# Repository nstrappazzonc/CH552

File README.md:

# Microcontroller CH552G by a hobbyist

This is a fascinating, enhanced, and well-equipped 8-bit microcontroller, available at an incredibly low cost (around $1), designed and manufactured in China by [Jiangsu Heng Qin Ltd. (WCH)](http://www.wch-ic.com). For now, we will focus on the [CH552G](https://www.wch-ic.com/products/CH552.html), which is based on the E8051 architecture. One of the most appealing features of this MCU is its USB port and a 24MHz internal oscillator, among other functionalities. Programming it requires a strong foundation in [MCS-51/80C51](https://en.wikipedia.org/wiki/MCS-51). The manufacturer provides a [package with a wide variety of source codes](https://www.wch.cn/downloads/CH552EVT_ZIP.html). There are different package options and versions of the MCU, such as the CH551, CH552, CH554, and CH559. The USB port, with its multiple functions, allows for easy program uploads, posing no risk as it is a native feature. In my personal opinion, this microcontroller is ideal for hobbyists working on simple projects or for those with a curious mindset.

A major difference of this microcontroller compared to other microcontrollers is that it does not require an additional device for programming; the USB port is sufficient. I believe that using a push button to access the bootloader for programming adds an extra level of security.

You can purchase the MCUs from the official store on [AliExpress](https://wchofficialstore.es.aliexpress.com/store/1100367542) or at [LCSC](https://www.lcsc.com).

For example, an MCU from the AT89LP51 family offers fewer features and costs three times more compared to the CH55X family. Of course, the support community for Microchip is much larger and more established compared to WCH’s, which is just starting to grow. However, the key is having good official documentation and a solid architecture. With patience and perseverance, great things can be achieved.

## Specifications

Here are the most relevant specifications of the MCU. For more details, refer to the [official documentation](https://www.wch-ic.com/products/CH552.html).

- Operates between 5V and 3.3V.
- Includes 16KB Code Flash, 1KB XRAM, 256B iRAM, and 128B DataFlash.
- Supports USB 2.0, UART, SPI, and ISP communication protocols.
- Features 3 timers, 2 signal capture units, 2 PWM, and 4 ADC.
- Equipped with a BootLoader.
- Includes a 24MHz internal clock.
- Comes with a unique numeric identifier.
- Available packages: TSSOP-20, SOP-16, MSOP-10.

The pinout we are showing is basic, just to give you an idea. There are more functionalities available on the ports. Please refer to the [datasheet](https://github.com/nstrappazzonc/CH552/blob/main/doc/CH552.pdf?raw=true) for more detailed information.

> [!IMPORTANT]
> 1. The internal 24MHz clock is not precise but in the most cases is good, you can adjust it by software using a logic analyze, otherwise you will have to use an external one.
> 2. It’s worth noting that there is a limitation with the ROM or Code Flash, as it uses an iFlash™ process, which can be programmed approximately 10,000 times before the Flash memory may begin to degrade or fail. However, this value can vary > slightly depending on factors such as operating temperature and proper handling of write cycles. In any case, it is enough.

## Minimum Schematic

Use the following components to build the minimum circuit:

- One CH552G microcontroller.
- Two 100nF capacitors.
- Two 10K resistors.
- Two 1K resistors.
- Two push buttons: one for boot and one for reset.

On the breadboard, it should look like this:

## Source Code

This repository contains a collection of example source codes written in C to get started. All the listed examples have been thoroughly tested to ensure they function correctly.

- [adc](https://github.com/nstrappazzonc/CH552/tree/main/src/adc) Captures voltage variations through an input port.
- [blink](https://github.com/nstrappazzonc/CH552/tree/main/src/blink) Uses an output port to turn an LED on and off.
- [bootloader](https://github.com/nstrappazzonc/CH552/tree/main/src/bootloader) Forces the MCU to enter bootloader mode by default.
- [button & led rgb](https://github.com/nstrappazzonc/CH552/tree/main/src/button_led_rgb) Interacts with a button and an RGB LED to change its color.
- [button](https://github.com/nstrappazzonc/CH552/tree/main/src/button) Uses one input port for a button and another output port for the LED.
- [cdc](https://github.com/nstrappazzonc/CH552/tree/main/src/cdc) Sends and receives messages via the UART protocol.
- [data flash](https://github.com/nstrappazzonc/CH552/tree/main/src/data_flash) Saves the last state in persistent memory.
- [DHT11](https://github.com/nstrappazzonc/CH552/tree/main/src/dht11) Read DHT11 sensor and print to OLED module.
- [fade](https://github.com/nstrappazzonc/CH552/tree/main/src/fade) Uses PWM to fade a LED on and off.
- [oled module](https://github.com/nstrappazzonc/CH552/tree/main/src/ssd1306) Simple usage of an OLED module with I2C.
- [USB/cdc](https://github.com/nstrappazzonc/CH552/tree/main/src/usb/cdc/tx) Sends messages via the USB port.

## Documentation

This is basic documentation to help you compile and upload firmware to the MCU, including the datasheet, relevant links, and much more.

- [SDCC (Small Devices C Compiler)](https://github.com/nstrappazzonc/CH552/blob/main/doc/sdcc.md) Explains how to install and use the compiler.
- [Bootloader](https://github.com/nstrappazzonc/CH552/blob/main/doc/flash.md) The MCU has a bootloader, and you need to know how to enter it to upload the firmware.
- [Datasheet](https://github.com/nstrappazzonc/CH552/blob/main/doc/CH552.pdf) Technical documentation from the manufacturer.

## Related Projects

- [CH334 - HUB USB 2.0](https://github.com/nstrappazzonc/CH334)
- [CH340 - USB 2.0 to Serial](https://github.com/nstrappazzonc/CH340)
- [CH9141 - Bluetooth Serial Transparent](https://github.com/nstrappazzonc/CH9141)

## Third-Party Projects

- [Adafruit CH552 QT Py](https://learn.adafruit.com/adafruit-ch552-qt-py/overview)
- [English Docs for CH559 Microcontroller](https://kprasadvnsi.github.io/CH559_Doc_English)
- [Small Devices Arduino for ch55x devices](https://github.com/DeqingSun/ch55xduino)

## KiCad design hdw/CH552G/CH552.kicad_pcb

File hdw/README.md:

# Hardware

En este directorio hay una serie de proyectos hechos con [KiCad](https://www.kicad.org) relacionados al CH552G.

Las placas se pueden mandar a construir en [JLCPCB](https://jlcpcb.com).

- [Minimal](https://github.com/nstrappazzonc/CH552/tree/main/hdw/minimal) Esquema mínimo del circuito para el CH552G.

- [Breakout SOIC16](https://github.com/nstrappazzonc/CH552/tree/main/hdw/SOIC16) Una simple PCB para poder soldar el CH552G y poder trabajar en el protoboard.

- [Breakout USB-C 2.0](https://github.com/nstrappazzonc/CH552/tree/main/hdw/USBC2) Una simple PCB para poder soldar el conector USB-C 2.0 y poder trabajar en el protoboard teniendo un excelente soporte que lo fija bien.

- [Breakout CH552G](https://github.com/nstrappazzonc/CH552/tree/main/hdw/CH552G) Una PCB con el circuito del CH552G.

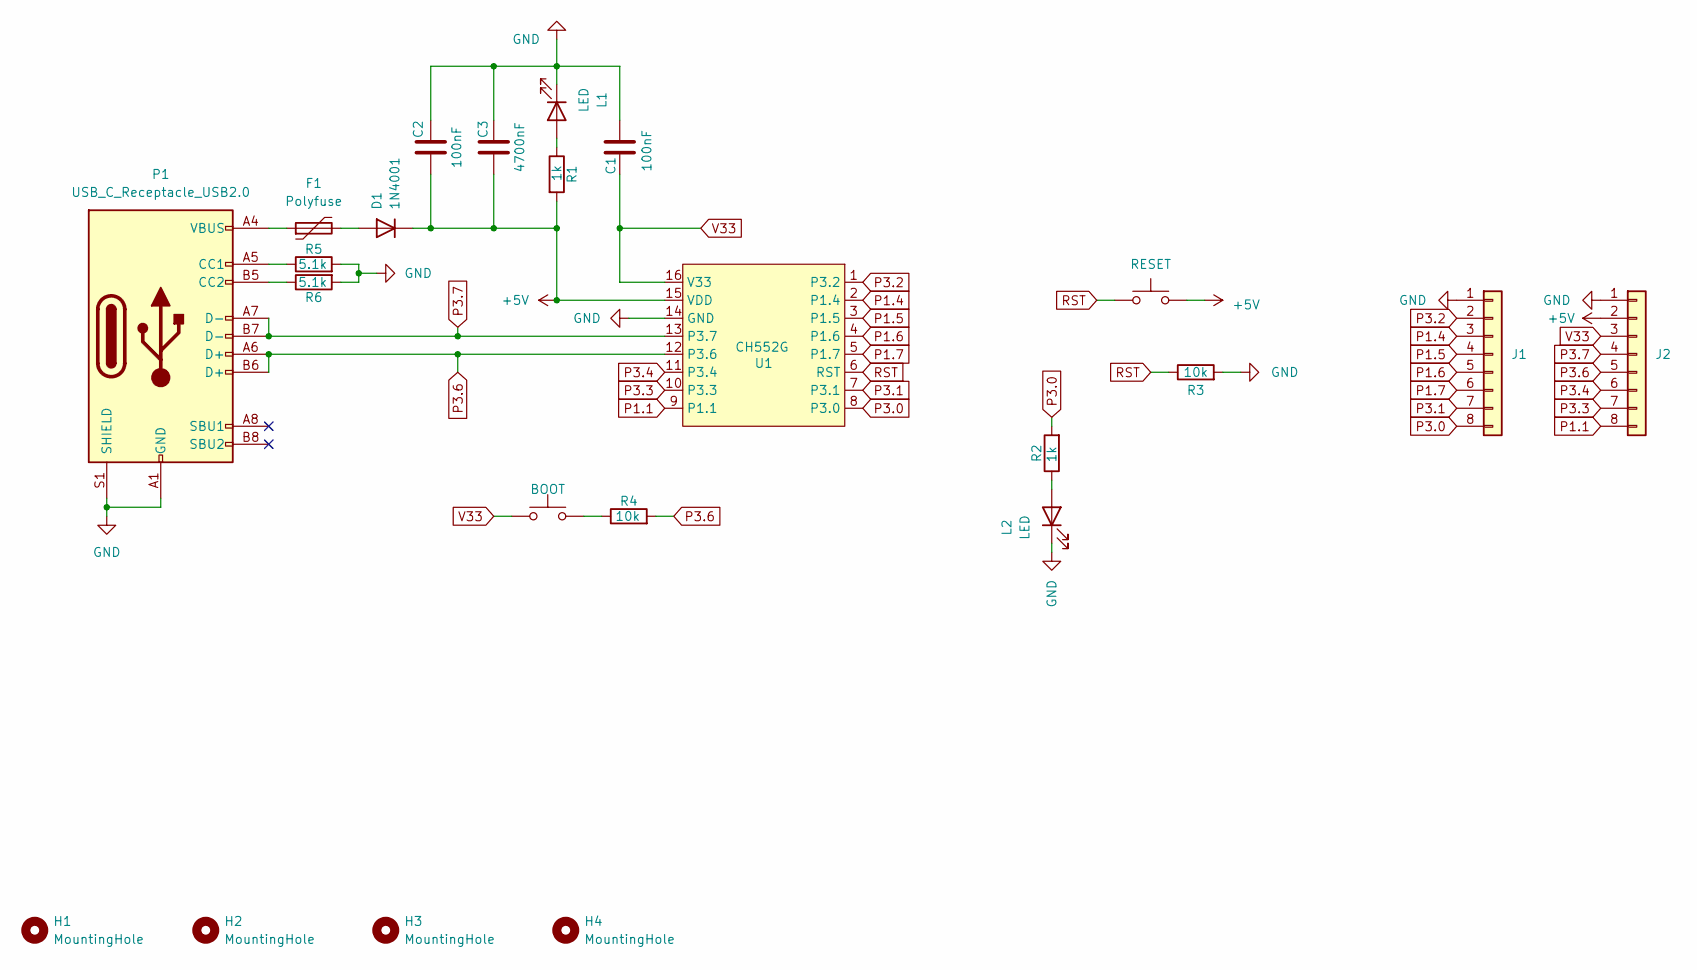
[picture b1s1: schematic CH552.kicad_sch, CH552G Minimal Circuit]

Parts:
C1, C2: 100nF; C1206
C3: 4700nF; C1206
D1: 1N4001; SMA_DO_214AC
F1: Polyfuse; F1206
H1, H2, H3, H4: MountingHole; MountingHole_3.2mm_M3
J1, J2: Conn_01x08; PinHeader_1x08_P2.54mm_Vertical
L1, L2: LED; L1206
P1: USB_C_Receptacle_USB2.0; USB_C_Receptacle_GCT_USB4105-xx-A_16P_TopMnt_Horizontal
R1, R2: 1k; R1206
R3, R4: 10k; R1206
R5, R6: 5.1k; R1206
SW1: RESET; SW_Push_SMD
SW2: BOOT; SW_Push_SMD
U1: CH552G; SOIC-16_3.9x9.9mm_P1.27mm

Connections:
+5V: C2.1, C3.1, D1.1 (K), J2.2, R1.2, SW1.1, U1.15 (VDD)
GND: C1.1, C2.2, C3.2, J1.1, J2.1, L1.1 (K), L2.1 (K), P1.A1 (GND), P1.A12 (GND), P1.B1 (GND), P1.B12 (GND), P1.S1 (SHIELD), R3.2, R5.2, R6.2, U1.14 (GND)
unnamed: D1.2 (A), F1.2
unnamed: F1.1, P1.A4 (VBUS), P1.A9 (VBUS), P1.B4 (VBUS), P1.B9 (VBUS)
unnamed: L1.2 (A), R1.1
unnamed: L2.2 (A), R2.1
unnamed: P1.A5 (CC1), R5.1
unnamed: P1.B5 (CC2), R6.1
unnamed: R4.1, SW2.2
P1.1: J2.8, U1.9 (P1.1)
P1.4: J1.3, U1.2 (P1.4)
P1.5: J1.4, U1.3 (P1.5)
P1.6: J1.5, U1.4 (P1.6)
P1.7: J1.6, U1.5 (P1.7)
P3.0: J1.8, R2.2, U1.8 (P3.0)
P3.1: J1.7, U1.7 (P3.1)
P3.2: J1.2, U1.1 (P3.2)
P3.3: J2.7, U1.10 (P3.3)
P3.4: J2.6, U1.11 (P3.4)
P3.6: J2.5, P1.A6 (D+), P1.B6 (D+), R4.2, U1.12 (P3.6)
P3.7: J2.4, P1.A7 (D-), P1.B7 (D-), U1.13 (P3.7)
RST: R3.1, SW1.2, U1.6 (RST)
V33: C1.2, J2.3, SW2.1, U1.16 (V33)

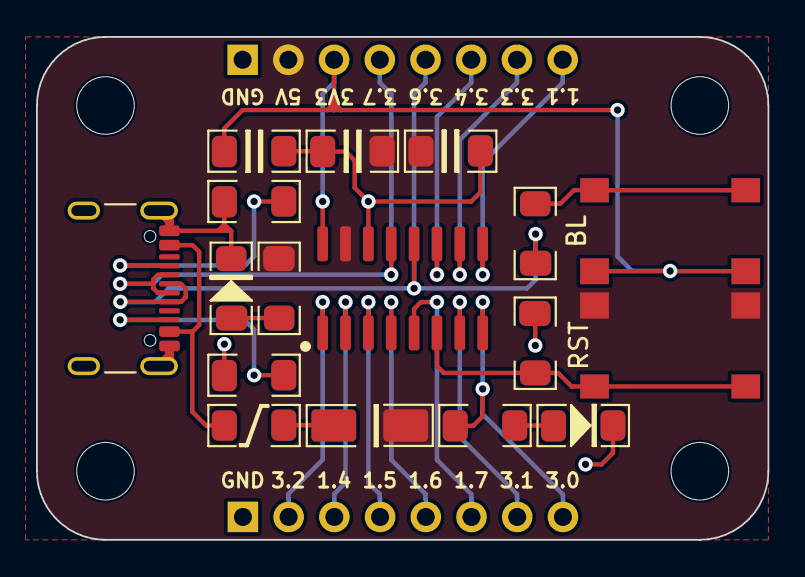
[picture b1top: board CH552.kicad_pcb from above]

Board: 2 copper layers, 40.6 x 27.9 mm, 23 parts (0 on the bottom side), 23 nets.

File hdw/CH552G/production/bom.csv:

Designator,Footprint,Quantity,Value,LCSC Part #
"C1, C2",C1206,2,100nF,
C3,C1206,1,4700nF,
D1,SMA_DO_214AC,1,1N4001,
F1,F1206,1,Polyfuse,
"H1, H2, H3, H4",MountingHole_3.2mm_M3,4,MountingHole,
"J1, J2",PinHeader_1x08_P2.54mm_Vertical,2,Conn_01x08,
"L1, L2",L1206,2,LED,
P1,USB_C_Receptacle_GCT_USB4105-xx-A_16P_TopMnt_Horizontal,1,USB_C_Receptacle_USB2.0,
"R1, R2",R1206,2,1k,
"R3, R4",R1206,2,10k,
"R5, R6",R1206,2,5.1k,
SW1,SW_Push_SMD,1,RESET,
SW2,SW_Push_SMD,1,BOOT,
U1,SOIC-16_3.9x9.9mm_P1.27mm,1,CH552G,

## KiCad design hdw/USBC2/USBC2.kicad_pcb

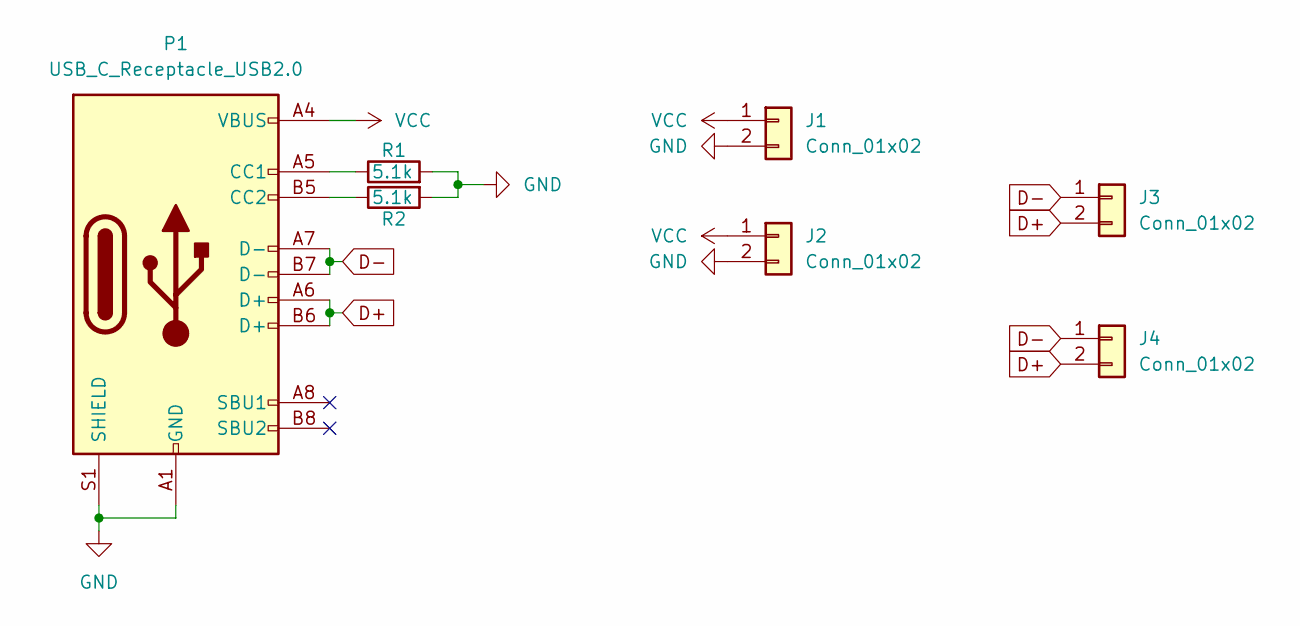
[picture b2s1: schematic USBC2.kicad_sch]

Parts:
J1, J2, J3, J4: Conn_01x02; PinHeader_1x02_P2.54mm_Vertical
P1: USB_C_Receptacle_USB2.0; USB_C_Receptacle_GCT_USB4105-xx-A_16P_TopMnt_Horizontal
R1, R2: 5.1k; R_1206_3216Metric_Pad1.30x1.75mm_HandSolder

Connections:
D+: J3.2, J4.2, P1.A6 (D+), P1.B6 (D+)
D-: J3.1, J4.1, P1.A7 (D-), P1.B7 (D-)
GND: J1.2, J2.2, P1.A1 (GND), P1.A12 (GND), P1.B1 (GND), P1.B12 (GND), P1.S1 (SHIELD), R1.2, R2.2
unnamed: P1.A5 (CC1), R1.1
unnamed: P1.B5 (CC2), R2.1
VCC: J1.1, J2.1, P1.A4 (VBUS), P1.A9 (VBUS), P1.B4 (VBUS), P1.B9 (VBUS)

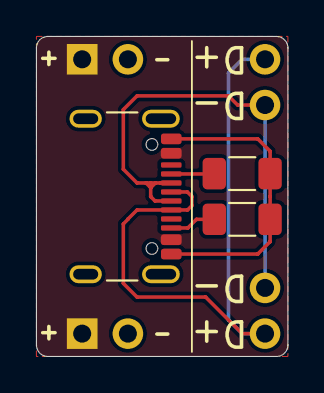
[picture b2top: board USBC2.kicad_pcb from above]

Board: 2 copper layers, 14.0 x 17.8 mm, 7 parts (0 on the bottom side), 6 nets.

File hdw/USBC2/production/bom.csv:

Designator,Footprint,Quantity,Value,LCSC Part #
"J1, J2, J3, J4",PinHeader_1x02_P2.54mm_Vertical,4,Conn_01x02,
P1,USB_C_Receptacle_GCT_USB4105-xx-A_16P_TopMnt_Horizontal,1,USB_C_Receptacle_USB2.0,
"R1, R2",1206,2,5.1k,

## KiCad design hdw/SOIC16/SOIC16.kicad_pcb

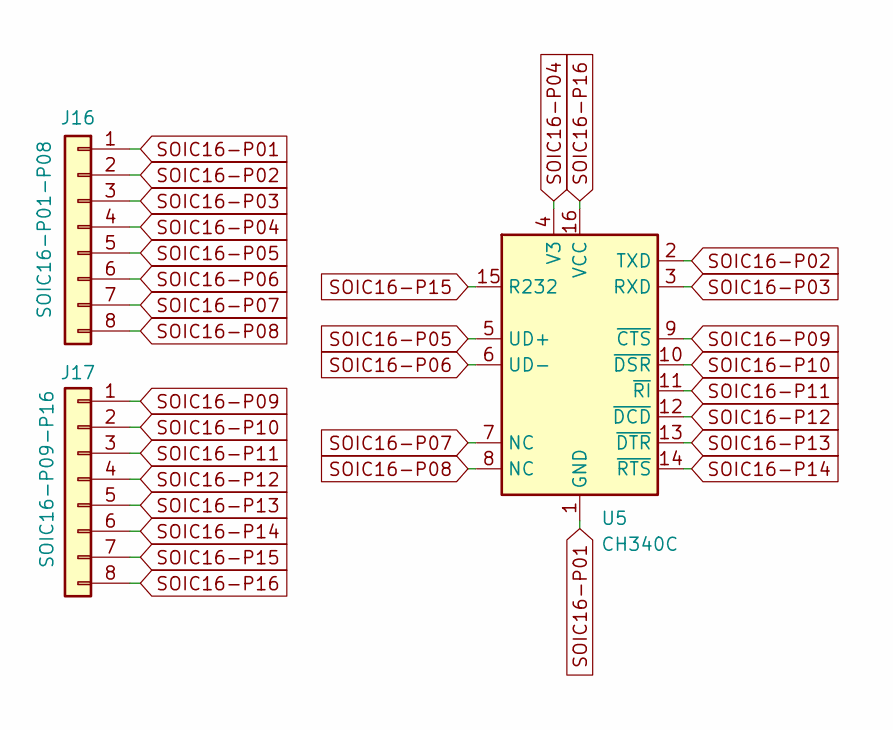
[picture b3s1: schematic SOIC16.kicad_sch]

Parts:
J16: SOIC16-P01-P08; PinHeader_1x08_P2.54mm_Vertical
J17: SOIC16-P09-P16; PinHeader_1x08_P2.54mm_Vertical
U5: CH340C; SOIC-16_3.9x9.9mm_P1.27mm

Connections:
SOIC16-P01: J16.1, U5.1 (GND)
SOIC16-P02: J16.2, U5.2 (TXD)
SOIC16-P03: J16.3, U5.3 (RXD)
SOIC16-P04: J16.4, U5.4 (V3)
SOIC16-P05: J16.5, U5.5 (UD+)
SOIC16-P06: J16.6, U5.6 (UD-)
SOIC16-P07: J16.7, U5.7 (NC)
SOIC16-P08: J16.8, U5.8 (NC)
SOIC16-P09: J17.1, U5.9 (~CTS)
SOIC16-P10: J17.2, U5.10 (~DSR)
SOIC16-P11: J17.3, U5.11 (~RI)
SOIC16-P12: J17.4, U5.12 (~DCD)
SOIC16-P13: J17.5, U5.13 (~DTR)
SOIC16-P14: J17.6, U5.14 (~RTS)
SOIC16-P15: J17.7, U5.15 (R232)
SOIC16-P16: J17.8, U5.16 (VCC)

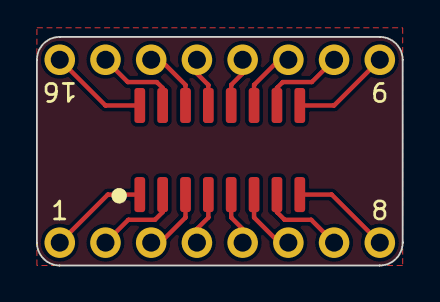
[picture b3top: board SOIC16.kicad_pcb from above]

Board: 2 copper layers, 20.3 x 12.7 mm, 3 parts (0 on the bottom side), 16 nets.

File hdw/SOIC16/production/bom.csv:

Designator,Footprint,Quantity,Value,LCSC Part #
J16,PinHeader_1x08_P2.54mm_Vertical,1,SOIC16-P01-P08,
J17,PinHeader_1x08_P2.54mm_Vertical,1,SOIC16-P09-P16,
U5,SOIC-16_3.9x9.9mm_P1.27mm,1,CH340C,

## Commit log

2023-12-21 doc - update
2023-12-23 some changes
2023-12-24 same changes
2023-12-26 feat - add cdc
2023-12-27 feat - implement own ch552.h
2023-12-28 fix - own ch552.h
2023-12-28 feat - add pinout on readme.
2023-12-28 doc - update readme.
2023-12-28 doc - update img.pinout2.png
2023-12-28 feat - add hardware projects wich kicad.
2023-12-30 feat - add adc example and definition on header.
2024-01-03 clear code and doc
2024-01-04 feat - usb
2024-01-04 remove dead code
2024-01-04 remove dead code II
2024-01-04 refactoring usb print.
2024-01-04 refact usb cdc functions ii
2024-01-04 refact usb cdc functions iii
2024-01-06 refact usb cdc functions iv
2024-01-06 doc - update links
2024-01-13 feat - breakout CH552G v2.0
2024-01-18 doc - schematic for blink
2024-06-10 update doc
2024-12-15 Save changes at: 1734300643
2024-12-15 Save changes at: 1734300742
2024-12-15 Save changes at: 1734300861
2024-12-15 Save changes at: 1734300961
2024-12-15 Save changes at: 1734301798
2024-12-15 Save changes at: 1734302091
2024-12-15 Save changes at: 1734302360
2024-12-15 Save changes at: 1734302413
2024-12-16 Save changes at: 1734347778
2024-12-20 Save changes at: 1734737068
2024-12-20 Save changes at: 1734737195
2024-12-21 Save changes at: 1734799249
2024-12-23 Save changes at: 1734985773
2024-12-23 Save changes at: 1734996890
2024-12-23 Save changes at: 1734996938
2024-12-23 Save changes at: 1734996963
2024-12-24 Save changes at: 1735036445
2024-12-24 Save changes at: 1735036816
2024-12-24 Save changes at: 1735037145
2024-12-24 Save changes at: 1735038115
2024-12-24 Save changes at: 1735053425
2024-12-24 Save changes at: 1735055324
2024-12-24 Save changes at: 1735055385
2024-12-24 Save changes at: 1735078625
2024-12-24 Save changes at: 1735082746
2024-12-24 Save changes at: 1735082926
2024-12-25 Save changes at: 1735170371
2024-12-25 Save changes at: 1735170439
2024-12-25 Save changes at: 1735170745
2024-12-25 Save changes at: 1735170856
2024-12-26 Save changes at: 1735211314
2024-12-26 Save changes at: 1735214951
2024-12-26 Save changes at: 1735251436
2024-12-26 Save changes at: 1735251710
2024-12-26 Save changes at: 1735251742
2024-12-26 Save changes at: 1735251883
2024-12-26 Save changes at: 1735251927
2024-12-26 Save changes at: 1735251964
2024-12-27 Save changes at: 1735293653
2024-12-27 Save changes at: 1735294060
2024-12-27 Save changes at: 1735296363
2024-12-27 Save changes at: 1735296533
2024-12-28 Save changes at: 1735380152
2024-12-29 Save changes at: 1735434824
2024-12-29 Save changes at: 1735435153
2024-12-29 Save changes at: 1735468303
2024-12-29 Save changes at: 1735468381
2024-12-29 Save changes at: 1735468438
2024-12-29 Save changes at: 1735468506
2024-12-29 Save changes at: 1735468607
2024-12-29 Save changes at: 1735468956
2024-12-29 Save changes at: 1735469001
2024-12-29 Save changes at: 1735469072
2024-12-29 Save changes at: 1735469273
2024-12-29 Save changes at: 1735469350
2024-12-29 Save changes at: 1735469756
2024-12-29 Save changes at: 1735469801
2024-12-29 Save changes at: 1735504637
2024-12-29 Save changes at: 1735504905
2024-12-29 Save changes at: 1735505030
2024-12-29 Save changes at: 1735505799
2024-12-29 Save changes at: 1735508646
2024-12-29 Save changes at: 1735509178
2024-12-30 Save changes at: 1735521143
2024-12-30 Save changes at: 1735521994
2024-12-30 Save changes at: 1735522133
2024-12-30 Save changes at: 1735522759
2024-12-30 Save changes at: 1735522796
2024-12-30 Save changes at: 1735554034
2024-12-30 Save changes at: 1735554582
2024-12-30 Save changes at: 1735583340
2024-12-30 Save changes at: 1735591074
2024-12-31 Save changes at: 1735683496
2025-01-01 Save changes at: 1735691038
2025-01-01 Save changes at: 1735691224
2025-01-01 Save changes at: 1735691252
2025-01-01 Save changes at: 1735692964
2025-01-01 Save changes at: 1735730344
2025-01-01 Save changes at: 1735731954
2025-01-01 Save changes at: 1735733544
2025-01-01 Save changes at: 1735751497
2025-01-01 Save changes at: 1735760479
2025-01-01 Save changes at: 1735771309
2025-01-01 Save changes at: 1735771375
2025-01-01 Save changes at: 1735771700
2025-01-01 Save changes at: 1735771761
2025-01-01 Save changes at: 1735771884
2025-01-03 Save changes at: 1735905962
2025-01-03 Save changes at: 1735906053
2025-01-03 Save changes at: 1735906128
2025-01-03 Save changes at: 1735906269
2025-01-03 Save changes at: 1735906355
2025-01-03 Save changes at: 1735935554
2025-01-03 Save changes at: 1735947432
2025-01-04 Save changes at: 1735951867
2025-01-04 Save changes at: 1735951917
2025-01-04 Save changes at: 1735977300
2025-01-04 Save changes at: 1735978086
2025-01-04 Save changes at: 1735978100
2025-01-04 Save changes at: 1735978168
2025-01-04 Save changes at: 1735978227
2025-01-05 Save changes at: 1736073146
2025-01-05 Save changes at: 1736073195
2025-01-06 Save changes at: 1736185025
2025-01-06 Save changes at: 1736195498
2025-01-07 Save changes at: 1736239146
2025-01-09 Save changes at: 1736461490
2025-01-11 Save changes at: 1736623741
2025-01-11 Save changes at: 1736623805
2025-01-12 Save changes at: 1736640963
2025-01-12 Save changes at: 1736641151
2025-01-12 Save changes at: 1736641420
2025-01-12 Save changes at: 1736691999
2025-01-12 Save changes at: 1736704528
2025-01-12 Save changes at: 1736704640
2025-01-12 Save changes at: 1736705361
2025-01-12 Save changes at: 1736705640
2025-01-12 Save changes at: 1736705883
2025-01-15 Save changes at: 1736971276
2025-01-15 Save changes at: 1736983430
2025-01-15 Save changes at: 1736983709
2025-01-15 Save changes at: 1736984366
2025-01-17 Save changes at: 1737104804
2025-01-17 Save changes at: 1737105065
2025-01-17 Save changes at: 1737107170
2025-01-17 Save changes at: 1737108637
2025-01-17 Save changes at: 1737108958
2025-01-17 Save changes at: 1737109132
2025-01-17 Save changes at: 1737109179
2025-01-17 Save changes at: 1737109249
2025-01-18 Save changes at: 1737160281
2025-01-18 Save changes at: 1737200003
2025-01-19 Save changes at: 1737317557
2025-01-19 Save changes at: 1737317579
2025-01-19 Save changes at: 1737317627
2025-01-19 Save changes at: 1737324595
2025-01-20 Save changes at: 1737416557
2025-01-25 Save changes at: 1737800640
2025-01-25 Save changes at: 1737806671
2025-01-25 Save changes at: 1737806986
2025-01-25 Save changes at: 1737807044
2025-01-25 Save changes at: 1737807111
2025-01-25 Save changes at: 1737807235
2025-01-25 Save changes at: 1737821375
2025-01-25 Save changes at: 1737821502
2025-01-25 Save changes at: 1737822183
2025-01-25 Save changes at: 1737822290
2025-01-25 Save changes at: 1737822637
2025-01-25 Save changes at: 1737822709
2025-01-25 Save changes at: 1737826062
2025-01-25 Save changes at: 1737826139
2025-01-25 Save changes at: 1737826380
2025-01-25 Save changes at: 1737826644
2025-01-25 Save changes at: 1737826689
2025-01-25 Save changes at: 1737826721
2025-01-25 Save changes at: 1737826878
2025-01-25 Save changes at: 1737827158
2025-01-25 Save changes at: 1737838547
2025-01-27 Save changes at: 1737966952
2025-01-27 Save changes at: 1737967174
2025-01-27 Save changes at: 1737967254
2025-01-27 Save changes at: 1737967347
2025-01-27 Save changes at: 1738020124
2025-01-27 Save changes at: 1738020249
2025-01-27 Save changes at: 1738020315
2025-01-30 Save changes at: 1738230274
2025-02-01 Save changes at: 1738404251
2025-02-02 Save changes at: 1738455460
2025-02-02 Save changes at: 1738455502
2025-02-03 Save changes at: 1738574942
2025-02-03 Save changes at: 1738575043
2025-02-03 Save changes at: 1738575077
2025-02-03 Save changes at: 1738575109
2025-02-03 Save changes at: 1738575208
2025-02-03 Save changes at: 1738575294
2025-02-03 Save changes at: 1738575442
2025-02-03 Save changes at: 1738575594
2025-02-03 Save changes at: 1738575639
2025-02-03 Save changes at: 1738578516
2025-02-03 Save changes at: 1738578566
